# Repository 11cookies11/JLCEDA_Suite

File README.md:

# KiCad Agent Suite

Agent-assisted KiCad hardware development pipeline.

KiCad Agent Suite uses a structured source model to resolve parts, compile an
intermediate representation, validate it, and export KiCad projects.

## Software Architecture

The suite is organized as a layered toolchain. AI agents and humans edit a
structured circuit model, then the toolchain derives build artifacts, validation
reports, and KiCad output from that source.

```text
AI agent / human
  |
  v
CLI and agent entrypoints
  src/kicad_suite/cli.py
  src/kicad_suite/entrypoints/
  |
  v
Orchestration layer
  src/kicad_suite/orchestration/
  - workflow templates, task routing, pipeline coordination, post-processing
  |
  v
Application services
  src/kicad_suite/application_services/
  - project state, diagnostics, reports, part resolution, semantic gates
  |
  v
Domain core
  src/kicad_suite/domain/core/
  - circuit model IO, IR compiler, IR validator, netlist, simulation plan,
    pin management, KiCad execution plan
  |
  v
Adapters
  src/kicad_suite/adapters/
  - KiCad writers/runners, PCB generation, JLC/LCSC/EasyEDA, symbol and
    footprint resolution
  |
  v
Generated build/output artifacts
```

### Main Data Flow

```text
source/circuit-model.source.json
  -> resolve parts and project-local libraries
  -> build/circuit-model.resolved.json
  -> build/ir.v1.json
  -> build/ir-validation.json
  -> hardware semantic gate artifacts
     build/net-intents.v1.json
     build/pin-contracts.v1.json
     build/hardware-erc.v1.json
     build/export-gate.v1.json
  -> output/<topology>/*.kicad_*
  -> ERC classification and agent reports
  -> build/report.json and build/report.md
```

`source/circuit-model.source.json` is the only authoritative project model for
new projects. `build/` and `output/` are generated views of that source.

### Agent-Facing API

The stable agent entrypoint is:

```powershell
hwtool agent manifest
```

The `agent` command group exposes machine-readable lifecycle operations:

- `status`, `inspect`, `explain`, `diagnose`, `report`
- `build-ir`, `validate-ir`, `resolve-symbols`, `export-kicad`
- `run` and `patch` for controlled model edits through the Model API
- `workflow` for template-driven multi-step tasks
- `pins` for pin resource checks and assignments
- `jlc` for LCSC search, preview, and project-local downloads
- `semantic-gates` for listing, validating, proposing, and accepting semantic
  gate rules

Agents should prefer these commands over direct writes to generated artifacts.

### Validation and Gate Layers

The repository uses several validation layers with different responsibilities:

- IR validation checks structural correctness before KiCad export.
- Circuit sanity checks catch shorts, floating pins, and suspicious passives.
- Hardware semantic gates catch topology-level mistakes before export, such as
  missing USB-C CC pull-downs or unsafe power-path wiring.
- KiCad ERC runs on exported KiCad projects and is classified into agent-readable
  findings.
- Semantic gate proposals can be generated from hardware ERC findings and stored
  as reviewable project knowledge.

Semantic gate files live in:

```text
build/proposed-semantic-gates/*.gate.json   # generated review queue
source/semantic-gates/*.gate.json           # accepted project rules
resources/hardware-rules/builtin/           # reserved built-in rules
resources/hardware-rules/promoted/          # reserved promoted rules
```

### Source Tree Responsibilities

- `src/kicad_suite/cli.py`: command-line and agent command dispatch.
- `src/kicad_suite/domain/core/`: pure model compilation, validation, planning,
  and pin/resource logic.
- `src/kicad_suite/application_services/`: project-level services that combine
  domain logic with filesystem state, reports, diagnostics, and rule registries.
- `src/kicad_suite/orchestration/`: workflow templates, agent task generation,
  pipeline event logs, and build coordination.
- `src/kicad_suite/adapters/`: integrations with KiCad files/tools,
  EasyEDA/JLC/LCSC, symbol libraries, and PCB writers.
- `schemas/`: JSON schemas for source models, IR, API requests/results, reports,
  semantic gates, and generated sidecar artifacts.
- `scripts/`: standalone utility scripts, including the hardware semantic gate.
- `tests/`: regression tests for CLI commands, schemas, model APIs, semantic
  gates, KiCad generation, and fixture behavior.

## Project Layout

New projects use the split source/build layout:

```text
project/
  source/
    circuit-model.source.json
  build/
    circuit-model.resolved.json
    ir.v1.json
    ir-validation.json
    report.json
    report.md
  libraries/
    symbols/
    footprints/
    3dmodels/
  output/
    <topology>/
      <topology>.kicad_pro
      <topology>.kicad_sch
      <topology>.kicad_pcb
      <topology>.erc.json
      <topology>.erc.classification.json
      agent-report.json
```

Edit `source/circuit-model.source.json`. Treat `build/`, `output/`, logs, and
`project.state.json` as generated artifacts.

## Common Workflow

Run commands from a project directory:

```powershell
hwtool agent status --project .
hwtool agent inspect --project .
hwtool agent diagnose --project .
hwtool agent resolve-symbols --project . --timeout 120
hwtool agent build-ir --project .
hwtool agent validate-ir --project .
hwtool agent export-kicad --project .
hwtool agent report --project . --markdown
hwtool agent diagnose --project .
```

Do not export KiCad before IR validation passes.

## Examples

Editable example source models live under `examples/*/source/`.

- `examples/stm32f103-minimal-system/source/circuit-model.source.json`
- `examples/esp32c3-minimal-system/source/circuit-model.source.json`
- `examples/refactor-layout-demo/source/circuit-model.source.json`
- `examples/h618-agentboard-v1/source/circuit-model.source.json`

Generated example `build/`, `output/`, and downloaded project-local libraries are
not tracked in git. Regenerate them with the workflow above when needed.

## Development

Useful commands:

```powershell
python scripts/kas.py --help
python -m pytest
npm run jlc:search -- STM32F103C8T6
```

Repository-wide KiCad resource libraries live in `resources/kicad/`.

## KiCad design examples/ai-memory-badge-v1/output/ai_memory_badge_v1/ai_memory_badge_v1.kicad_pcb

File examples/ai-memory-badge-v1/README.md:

# AI Memory Badge V1

全天候随身 AI 记忆器原型项目。

本版本先定义产品需求和系统设计，不急于锁定完整原理图。目标是做一块可佩戴、可夹持、低功耗、以人声触发录音为核心的硬件原型板。

## Product Direction

- 形态：胸牌 / 夹子
- 录音策略：人声触发录音，支持手动标记重点片段
- 隐私策略：本地加密预留，录音状态可见，支持物理静音
- 同步方式：USB-C + Wi-Fi
- 设计优先级：续航优先，其次是可接受的人声清晰度
- 项目阶段：原型板，不追求第一版直接小型量产

## Documents

- `docs/00_requirements.md`：产品需求与约束
- `docs/01_system_architecture.md`：系统架构和模块划分
- `docs/02_design_decisions.md`：关键设计取舍
- `docs/03_hardware_design_plan.md`：硬件设计方案与验证计划
- `docs/04_component_selection.md`：Rev A 器件选型方向
- `docs/05_esp32s3_bare_chip_design.md`：ESP32-S3 裸芯片实现方案
- `docs/06_schematic_module_plan.md`：原理图模块拆分方案
- `docs/07_part_resolution_notes.md`：关键器件解析状态与候选料

## Next Step

确认需求后，下一步生成：

```text
source/circuit-model.source.json
```

并进入 KiCad Agent Suite 的标准流程：

```powershell
hwtool agent inspect --project .
hwtool agent resolve-symbols --project . --timeout 120
hwtool agent build-ir --project .
hwtool agent validate-ir --project .
hwtool agent export-kicad --project .
hwtool agent report --project . --markdown
```

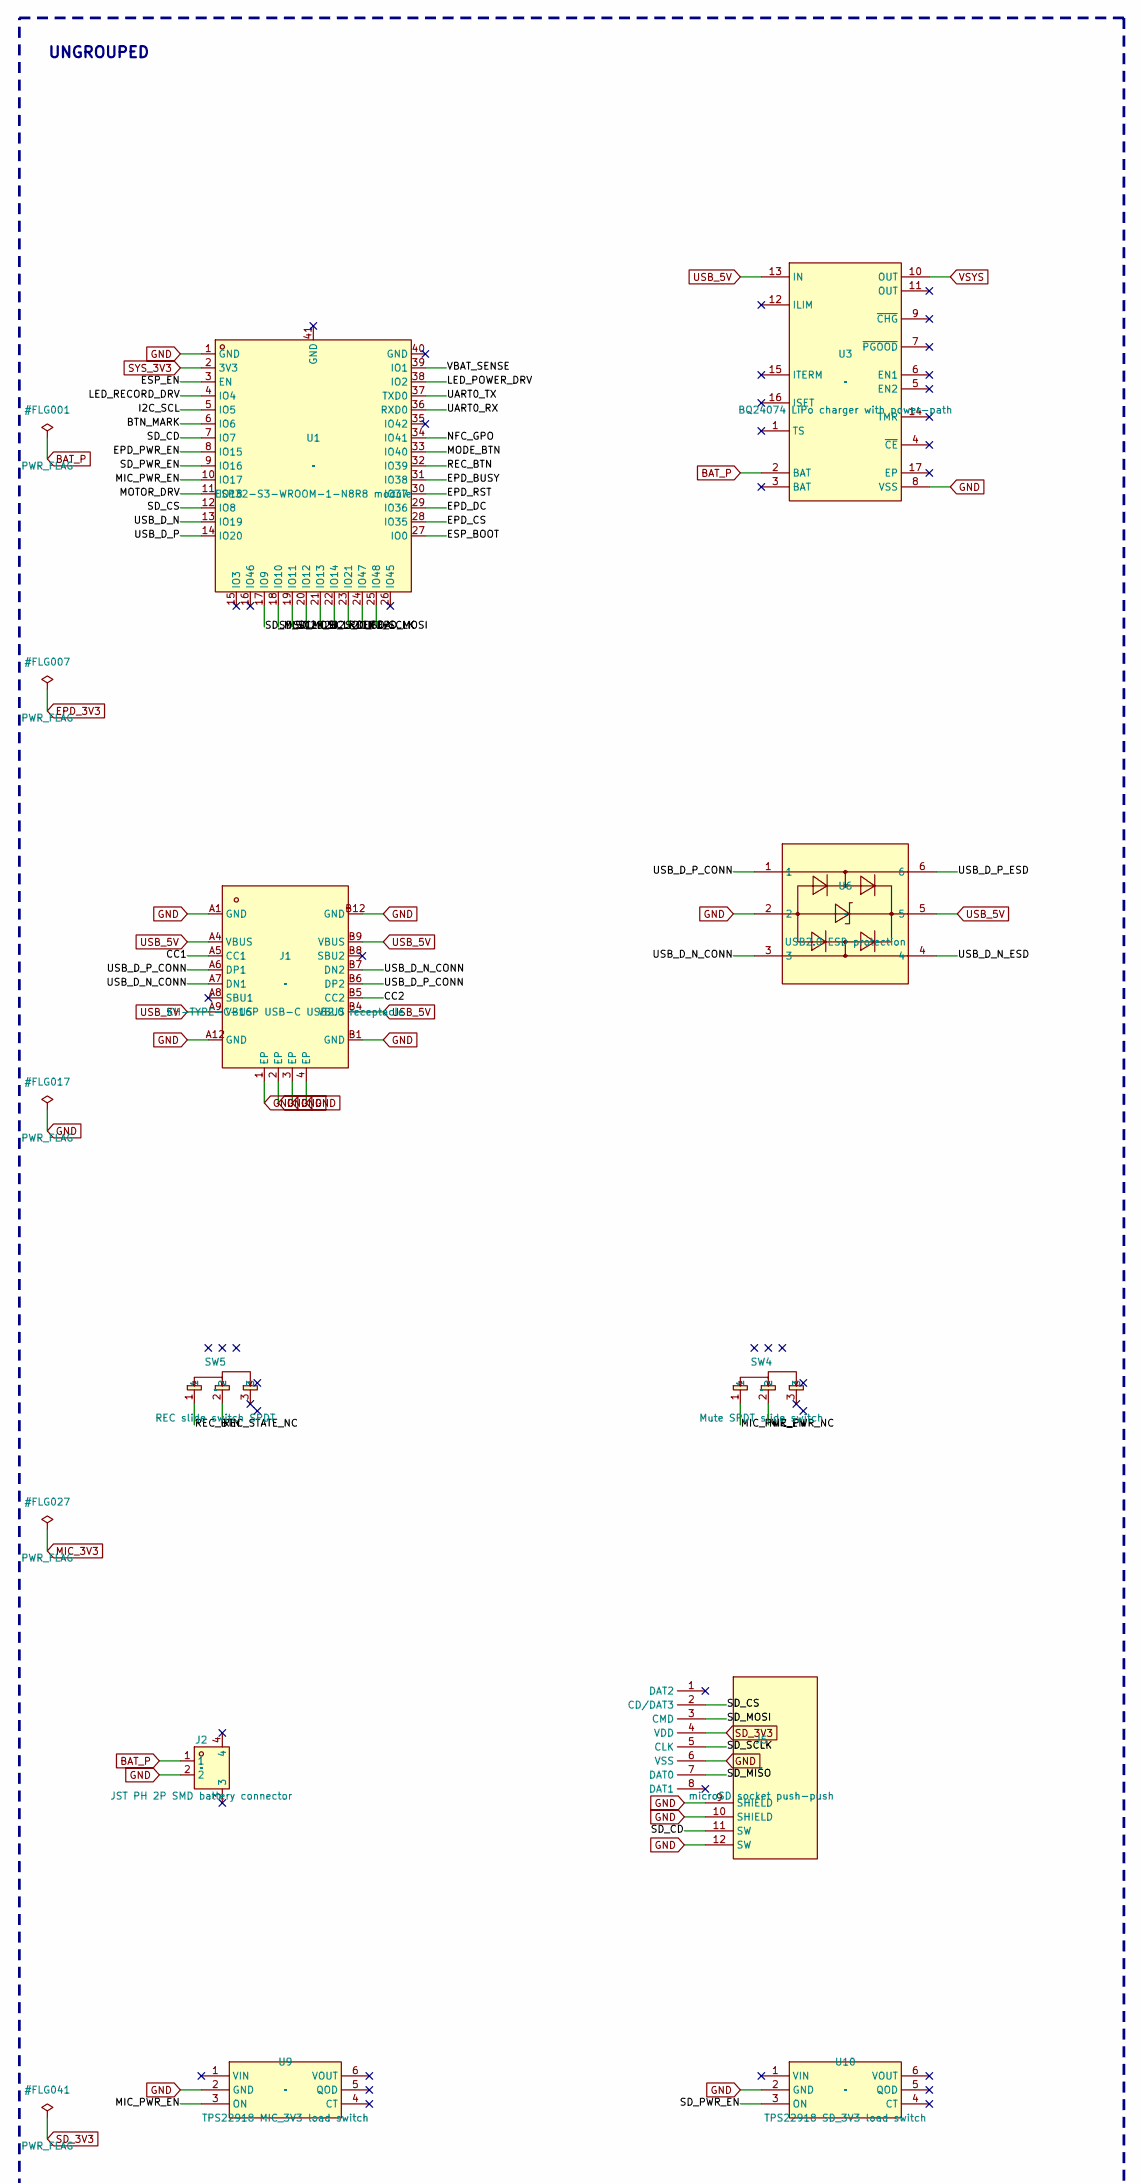
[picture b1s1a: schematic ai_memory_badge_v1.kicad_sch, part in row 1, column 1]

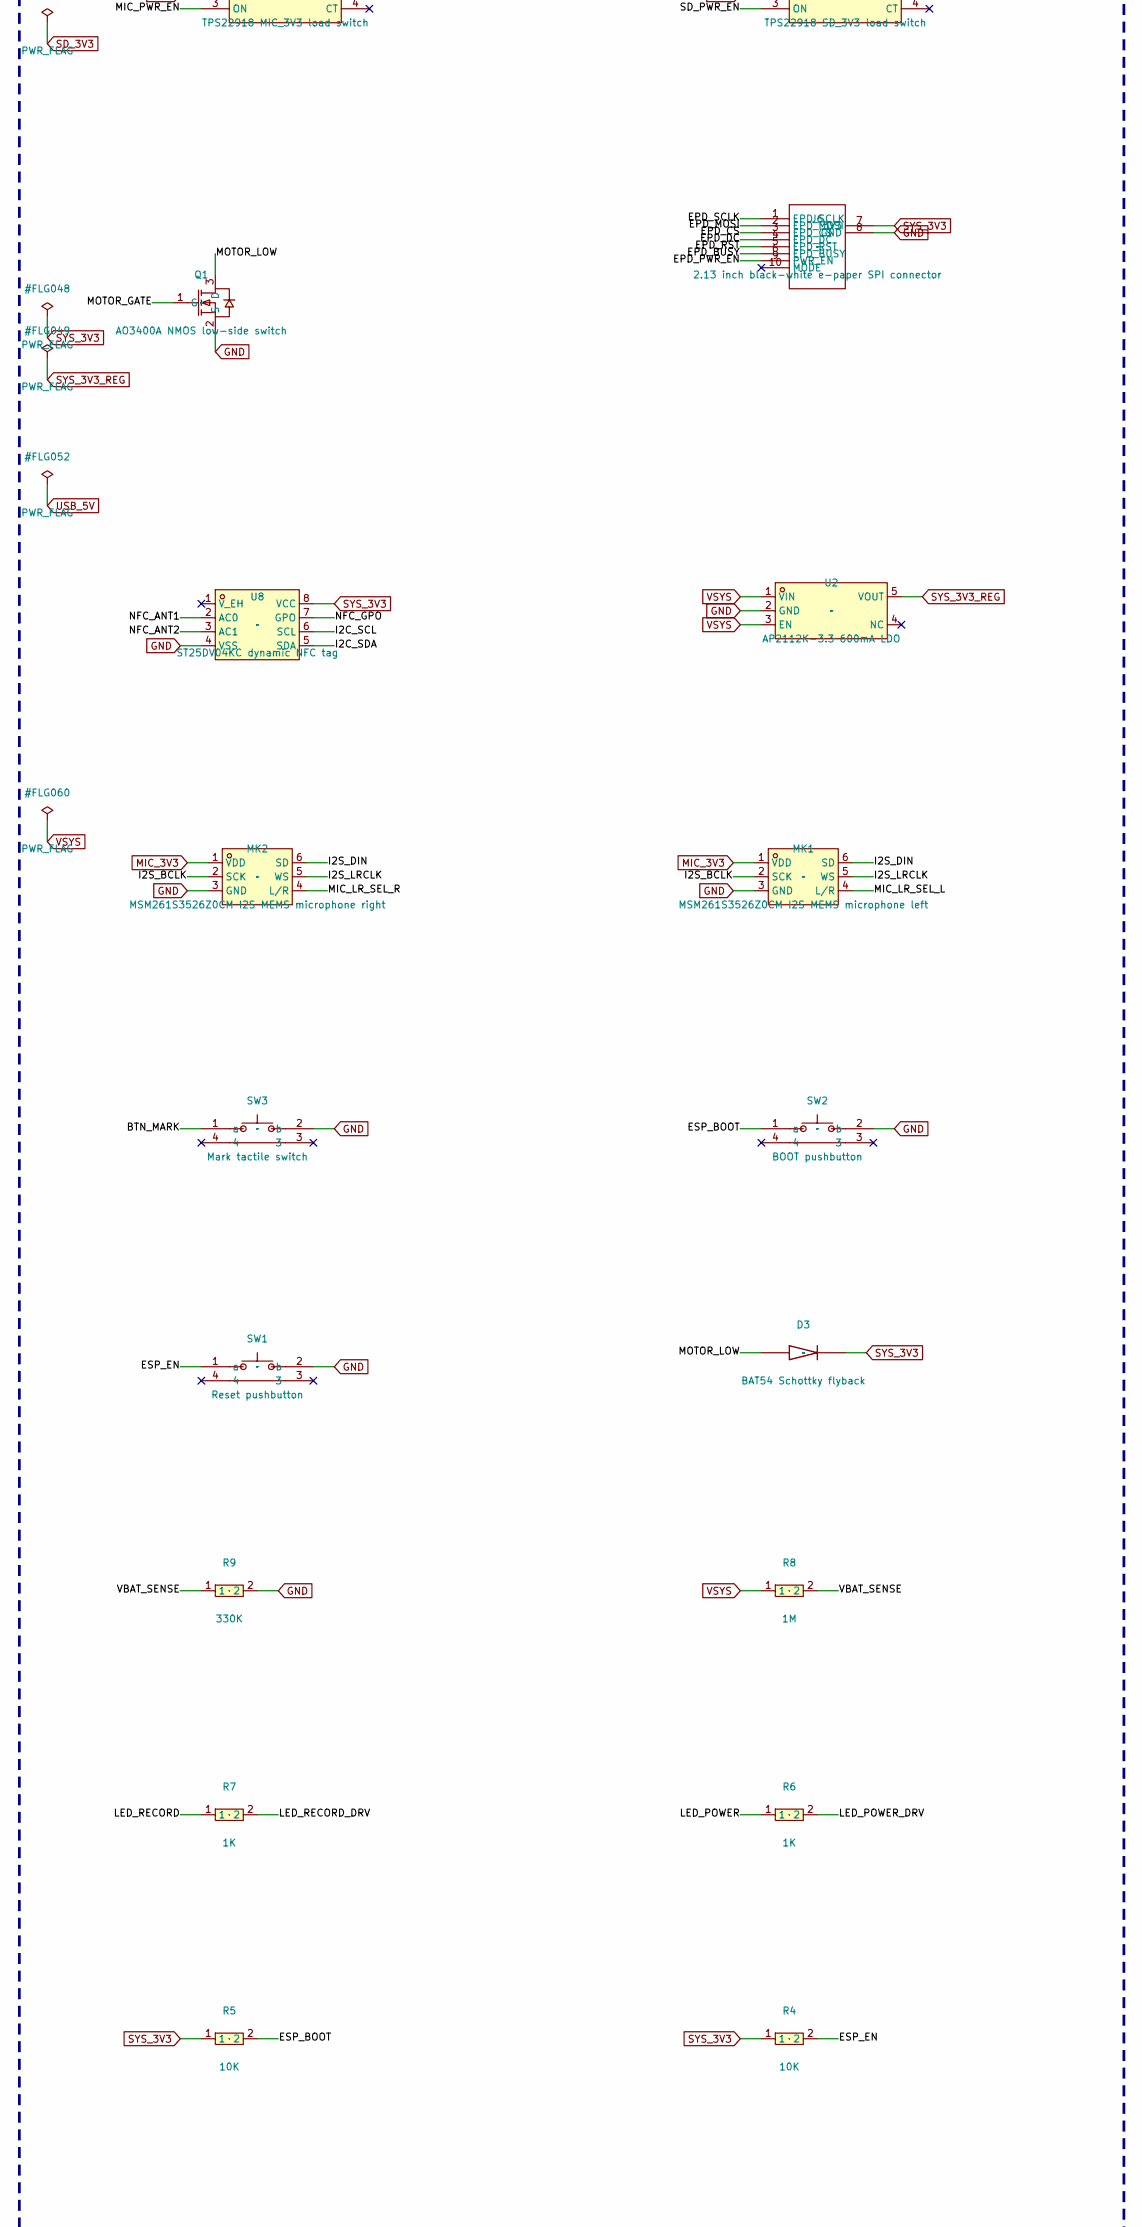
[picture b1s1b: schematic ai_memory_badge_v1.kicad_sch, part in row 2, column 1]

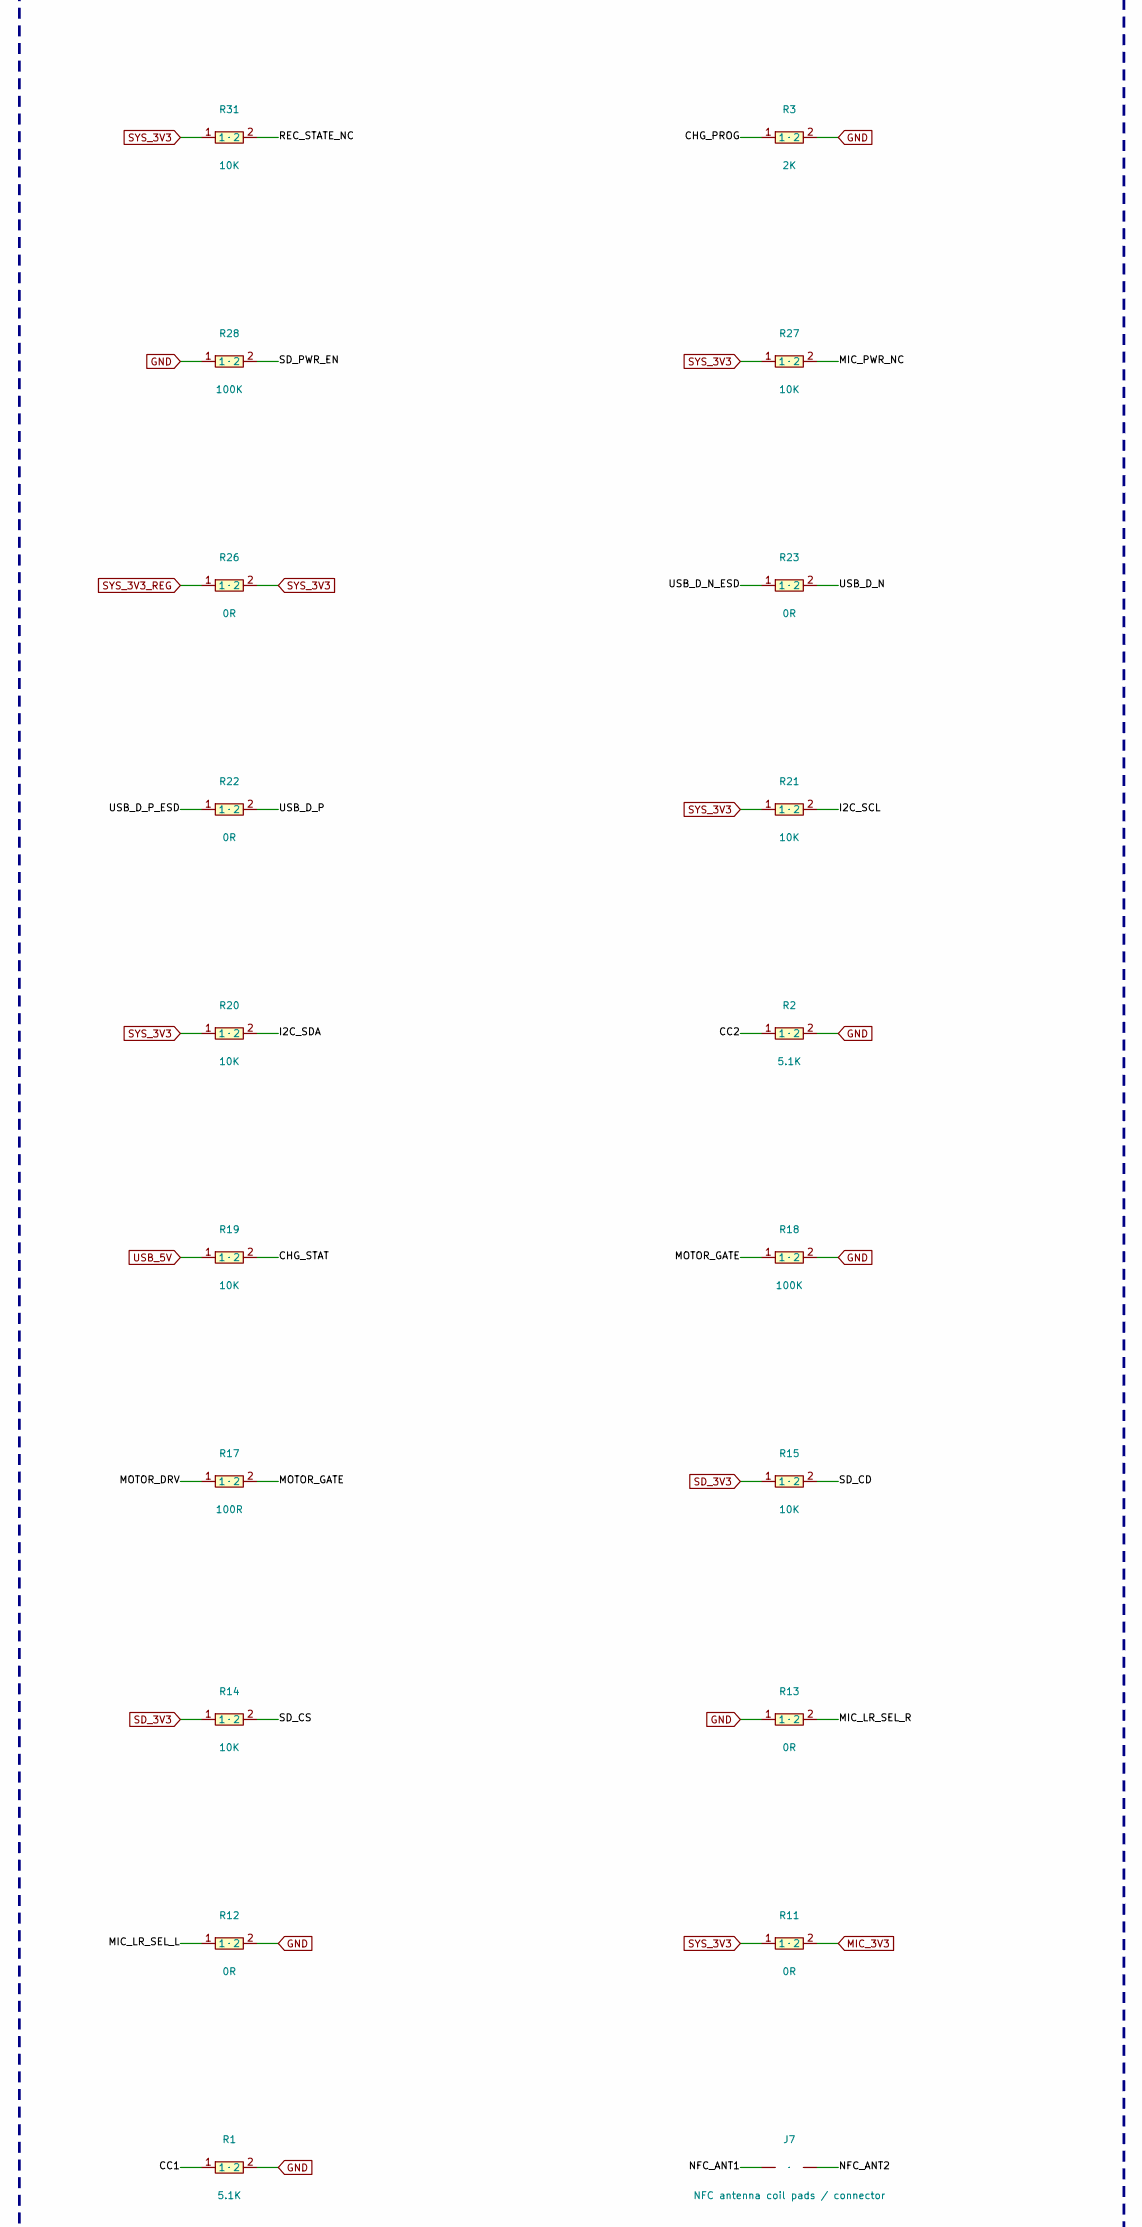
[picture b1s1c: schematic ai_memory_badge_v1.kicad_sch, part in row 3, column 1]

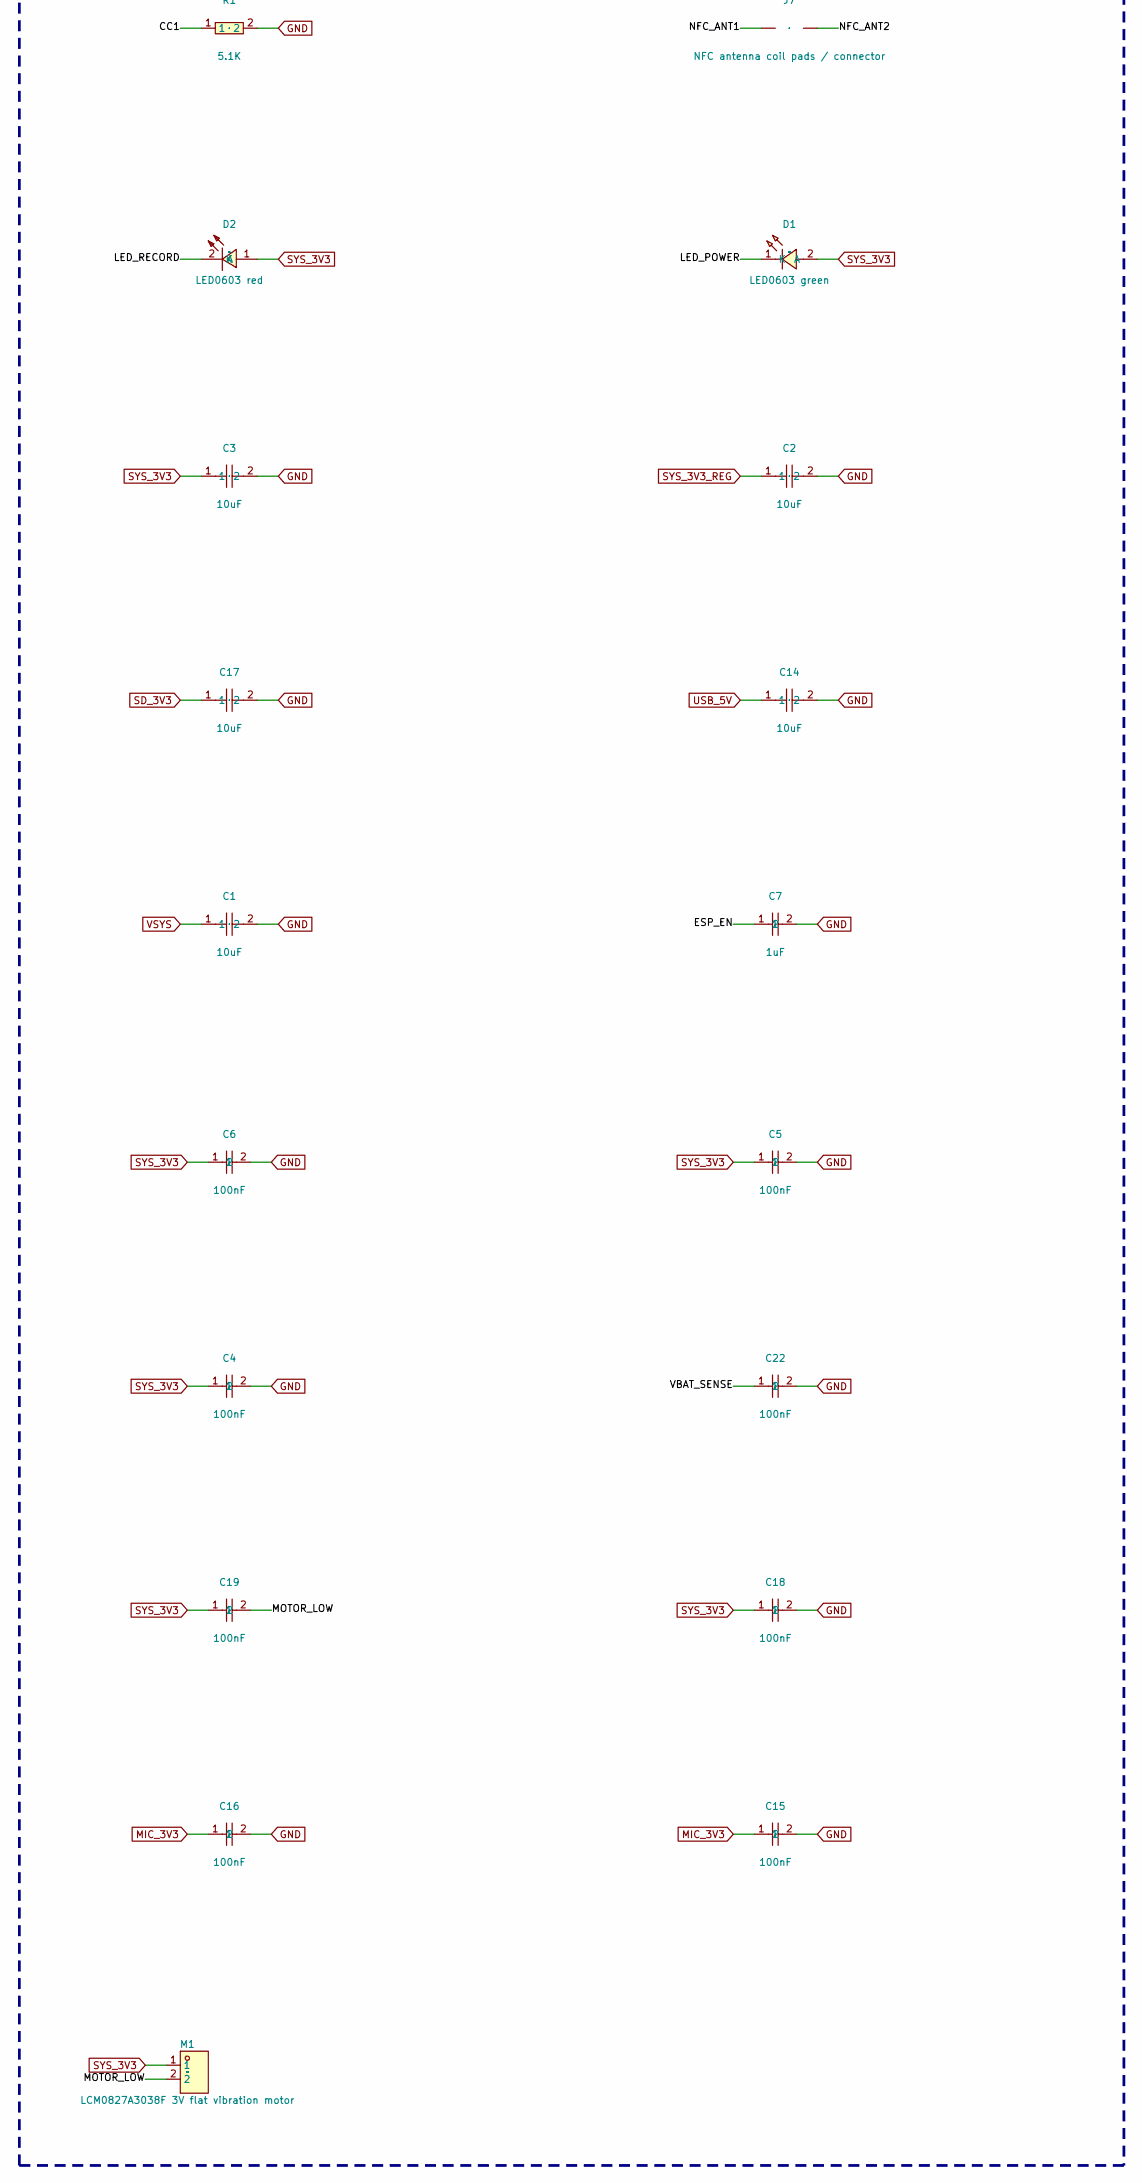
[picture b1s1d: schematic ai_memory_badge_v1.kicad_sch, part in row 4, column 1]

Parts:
C1, C2, C3, C14, C17: 10uF; C0603; LCSC C19702
C4, C5, C6, C15, C16, C18, C19, C22: 100nF; C0603; LCSC C1590
C7: 1uF; C0603; LCSC C1592
D1: LED0603 green; LED-SMD_L1.6-W0.8-RD_GREEN-1; LCSC C5139863
D2: LED0603 red; LED-SMD_L1.6-W0.8-R-RD; LCSC C2286
D3: BAT54 Schottky flyback; SOT-23-3_L2.9-W1.3-P1.90-LS2.4-BR; LCSC C131213
J1: KH-TYPE-C-16P USB-C USB2.0 receptacle; USB-C-SMD_KH-TYPE-C-16P; LCSC C709357
J2: JST PH 2P SMD battery connector; CONN-SMD_P2.00_S2B-PH-SM4-TB-LF-SN; LCSC C295747
J5: microSD socket push-push; TF-SMD_TF-001B; LCSC C125617
J6: 2.13 inch black-white e-paper SPI connector; FPC-SMD_24P-P0.50-L6.1-W16.4; LCSC C20688
J7: NFC antenna coil pads / connector; SMD-2P
M1: LCM0827A3038F 3V flat vibration motor; VIBRATIONMOTOR-TH_LCM0827A3038F; LCSC C2759981
MK1: MSM261S3526Z0CM I2S MEMS microphone left; MIC-SMD_6P-L3.5-W2.7-P0.90-TR; LCSC C966933
MK2: MSM261S3526Z0CM I2S MEMS microphone right; MIC-SMD_6P-L3.5-W2.7-P0.90-TR; LCSC C966933
Q1: AO3400A NMOS low-side switch; SOT-23-3_L2.9-W1.3-P1.90-LS2.4-BR; LCSC C20917
R1, R2: 5.1K; R0603; LCSC C23186
R3: 2K; R0603; LCSC C22975
R4, R5, R14, R15, R19, R20, R21, R27, R31: 10K; R0603; LCSC C15401
R6, R7: 1K; R0603; LCSC C14676
R8: 1M; R0603; LCSC C22935
R9: 330K; R0603; LCSC C23137
R11, R12, R13, R22, R23, R26: 0R; R0603; LCSC C21189
R17: 100R; R0603; LCSC C22775
R18, R28: 100K; R0603; LCSC C25803
SW1: Reset pushbutton; SW-SMD_K5-1617SA-02; LCSC C128964
SW2: BOOT pushbutton; SW-SMD_K5-1617SA-02; LCSC C128964
SW3: Mark tactile switch; SW-SMD_K5-1617SA-02; LCSC C128964
SW4: Mute SPDT slide switch; SW-SMD_MST-12D18G4-SPDT-SLIDE-SWITCH; LCSC C49023767
SW5: REC slide switch SPDT; SW-SMD_MST-12D18G4-SPDT-SLIDE-SWITCH; LCSC C49023767
U1: ESP32-S3-WROOM-1-N8R8 module; WIRELM-SMD_ESP32-S3-WROOM-1; LCSC C2913201
U2: AP2112K-3.3 600mA LDO; SOT-25-5_L2.9-W1.6-P0.95-LS2.8-BL; LCSC C51118
U3: BQ24074 LiPo charger with power-path; QFN-16_L3.0-W3.0-P0.50-TL-EP1.7; LCSC C54313
U6: USB2.0 ESD protection; SOT-23-6_L2.9-W1.6-P0.95-LS2.8-BL; LCSC C7519
U8: ST25DV04KC dynamic NFC tag; SO-8_L4.9-W3.9-P1.27-LS6.0-BL; LCSC C5221752
U9: TPS22918 MIC_3V3 load switch; SOT-23-6_L2.9-W1.6-P0.95-LS2.8-BL; LCSC C131941
U10: TPS22918 SD_3V3 load switch; SOT-23-6_L2.9-W1.6-P0.95-LS2.8-BL; LCSC C131941

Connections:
BAT_P: J2.1, U3.2 (BAT)
BTN_MARK: SW3.1 (a), U1.6 (IO6)
CC1: J1.A5 (CC1), R1.1
CC2: J1.B5 (CC2), R2.1
CHG_PROG: R3.1, U3.16 (ISET)
CHG_STAT: R19.2, U3.9 (~CHG)
EPD_BUSY: J6.6 (EPD_BUSY), U1.31 (IO38)
EPD_CS: J6.3 (EPD_CS), U1.28 (IO35)
EPD_DC: J6.4 (EPD_DC), U1.29 (IO36)
EPD_MOSI: J6.2 (EPD_MOSI), U1.25 (IO48)
EPD_PWR_EN: J6.9 (PWR_EN), U1.8 (IO15)
EPD_RST: J6.5 (EPD_RST), U1.30 (IO37)
EPD_SCLK: J6.1 (EPD_SCLK), U1.24 (IO47)
ESP_BOOT: R5.2, SW2.1 (a), U1.27 (IO0)
ESP_EN: C7.1, R4.2, SW1.1 (a), U1.3 (EN)
GND: C1.2, C2.2, C3.2, C4.2, C5.2, C6.2, C7.2, C14.2, C15.2, C16.2, C17.2, C18.2, C22.2, J1.1 (EP), J1.2 (EP), J1.3 (EP), J1.4 (EP), J1.A1 (GND), J1.A12 (GND), J1.B1 (GND), J1.B12 (GND), J2.2, J5.6 (VSS), J5.9 (SHIELD), J5.10 (SHIELD), J5.12 (SW), J6.8 (GND), MK1.3 (GND), MK2.3 (GND), Q1.2 (S), R1.2, R2.2, R3.2, R9.2, R12.2, R13.1, R18.2, R28.1, SW1.2 (b), SW2.2 (b), SW3.2 (b), U1.1 (GND), U2.2 (GND), U3.8 (VSS), U6.2, U8.4 (VSS), U9.2 (GND), U10.2 (GND)
I2C_SCL: R21.2, U1.5 (IO5), U8.6 (SCL)
I2C_SDA: R20.2, U1.23 (IO21), U8.5 (SDA)
I2S_BCLK: MK1.2 (SCK), MK2.2 (SCK), U1.20 (IO12)
I2S_DIN: MK1.6 (SD), MK2.6 (SD), U1.22 (IO14)
I2S_LRCLK: MK1.5 (WS), MK2.5 (WS), U1.21 (IO13)
LED_POWER: D1.1 (K), R6.1
LED_POWER_DRV: R6.2, U1.38 (IO2)
LED_RECORD: D2.2 (K), R7.1
LED_RECORD_DRV: R7.2, U1.4 (IO4)
MIC_3V3: C15.1, C16.1, MK1.1 (VDD), MK2.1 (VDD), R11.2, U9.6 (VOUT)
MIC_LR_SEL_L: MK1.4 (L/R), R12.1
MIC_LR_SEL_R: MK2.4 (L/R), R13.2
MIC_PWR_EN: SW4.1, U1.10 (IO17), U9.3 (ON)
MIC_PWR_NC: R27.2, SW4.2
MODE_BTN: U1.33 (IO40)
MOTOR_DRV: R17.1, U1.11 (IO18)
MOTOR_GATE: Q1.1 (G), R17.2, R18.1
MOTOR_LOW: C19.2, D3.1 (A), M1.2, Q1.3 (D)
NFC_ANT1: J7.1 (AC0), U8.2 (AC0)
NFC_ANT2: J7.2 (AC1), U8.3 (AC1)
NFC_GPO: U1.34 (IO41), U8.7 (GPO)
REC_BTN: SW5.1, U1.32 (IO39)
REC_STATE_NC: R31.2, SW5.2
SD_3V3: C17.1, J5.4 (VDD), R14.1, R15.1, U10.6 (VOUT)
SD_CD: J5.11 (SW), R15.2, U1.7 (IO7)
SD_CS: J5.2 (CD/DAT3), R14.2, U1.12 (IO8)
SD_MISO: J5.7 (DAT0), U1.17 (IO9)
SD_MOSI: J5.3 (CMD), U1.19 (IO11)
SD_PWR_EN: R28.2, U1.9 (IO16), U10.3 (ON)
SD_SCLK: J5.5 (CLK), U1.18 (IO10)
SYS_3V3: C3.1, C4.1, C5.1, C6.1, C18.1, C19.1, D1.2 (A), D2.1 (A), D3.2 (K), J6.7 (3V3), M1.1, R4.1, R5.1, R11.1, R20.1, R21.1, R26.2, R27.1, R31.1, U1.2 (3V3), U8.8 (VCC), U9.1 (VIN), U10.1 (VIN)
SYS_3V3_REG: C2.1, R26.1, U2.5 (VOUT)
UART0_RX: U1.36 (RXD0)
UART0_TX: U1.37 (TXD0)
USB_5V: C14.1, J1.A4 (VBUS), J1.A9 (VBUS), J1.B4 (VBUS), J1.B9 (VBUS), R19.1, U3.13 (IN), U6.5
USB_D_N: R23.2, U1.13 (IO19)
USB_D_N_CONN: J1.A7 (DN1), J1.B7 (DN2), U6.3
USB_D_N_ESD: R23.1, U6.4
USB_D_P: R22.2, U1.14 (IO20)
USB_D_P_CONN: J1.A6 (DP1), J1.B6 (DP2), U6.1
USB_D_P_ESD: R22.1, U6.6
VBAT_SENSE: C22.1, R8.2, R9.1, U1.39 (IO1)
VSYS: C1.1, R8.1, U2.1 (VIN), U2.3 (EN), U3.10 (OUT)

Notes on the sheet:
UNGROUPED

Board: 2 copper layers, 62 parts (0 on the bottom side), 54 nets, no tracks yet.

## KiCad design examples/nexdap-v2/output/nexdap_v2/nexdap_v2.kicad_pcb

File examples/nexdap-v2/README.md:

# nexdap-esp32c3-managed-rp2040-swd-coprocessor-v2

This example is a starter workspace for the nexdap-esp32c3-managed-rp2040-swd-coprocessor-v2 project.

Project intent:

- Start from a generic hardware project template
- Keep the workspace ready for schematic, PCB, release, and validation artifacts
- Let the hardware model define the actual target platform and BOM

Current status:

- Requirements captured in `docs/00_requirements.md`
- Architecture and bring-up documents are scaffolded
- Hardware workspaces are ready for detail work

Recommended next steps:

1. Freeze requirements in `docs/00_requirements.md`
2. Draft the system architecture in `docs/01_system_architecture.md`
3. Create `source/circuit-model.source.json` when the interface list is stable
4. Let the toolchain generate `build/circuit-model.resolved.json`

Generated project slug: `nexdap-v2`

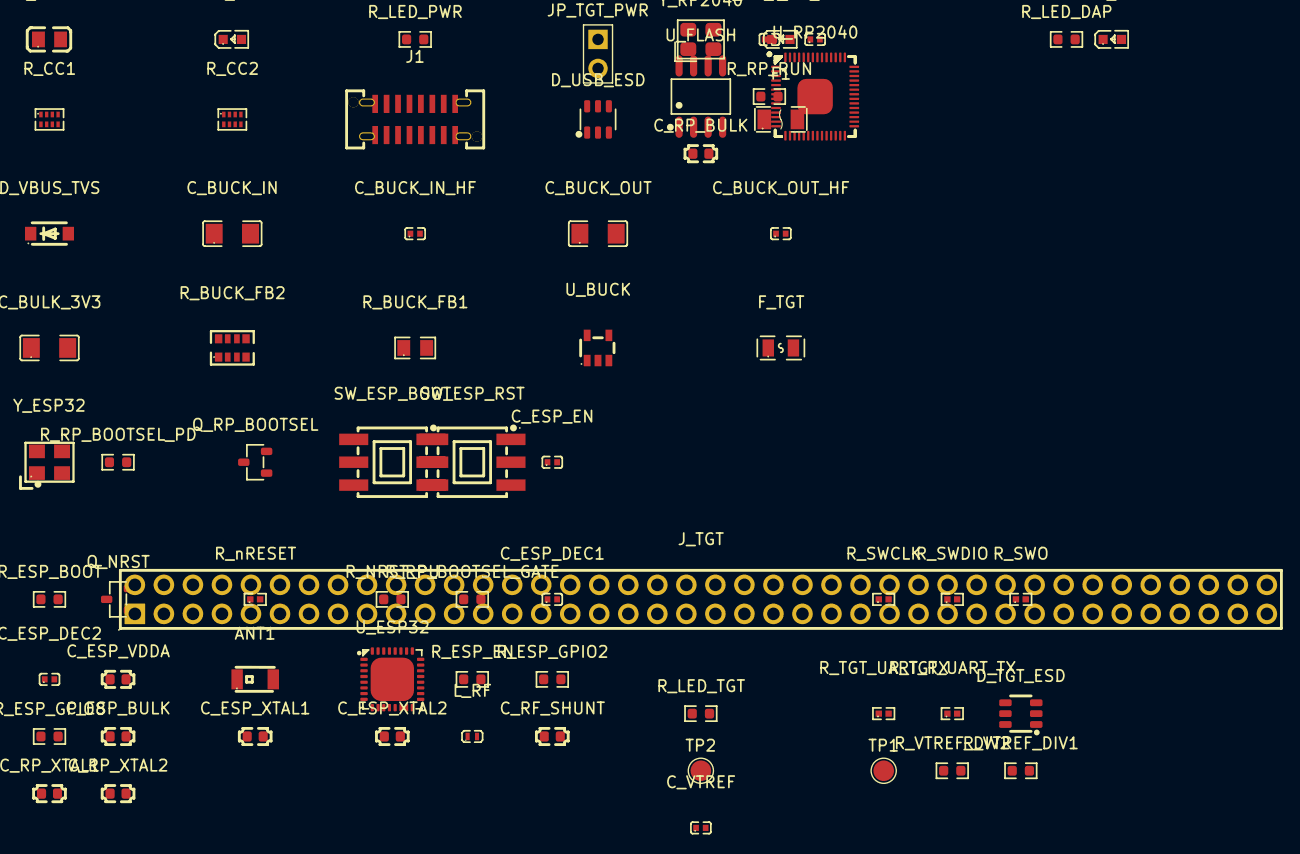
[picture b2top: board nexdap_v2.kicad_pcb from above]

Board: 2 copper layers, 68 parts (0 on the bottom side), 57 nets, no tracks yet.

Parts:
ANT1: 2450AT18A100E; ANT-SMD_L3.2-W1.6
C_BUCK_IN: 22uF; C1206
C_BUCK_IN_HF: 100nF; C0402
C_BUCK_OUT: 22uF; C1206
C_BUCK_OUT_HF: 100nF; C0402
C_BULK_3V3: 22uF; C1206
C_ESP_BULK: 4.7uF; C0603
C_ESP_DEC1, C_ESP_DEC2: 0.1uF; C0402
C_ESP_EN: 0.1uF; C0402
C_ESP_VDDA: 1uF; C0603
C_ESP_XTAL1, C_ESP_XTAL2: 22pF; C0603
C_RF_SHUNT: 1.2pF; C0603
C_RP_BULK: 4.7uF; C0603
C_RP_DEC1, C_RP_DEC2: 0.1uF; C0402
C_RP_XTAL1, C_RP_XTAL2: 22pF; C0603
C_VTREF: 0.1uF; C0402
D_TGT_ESD: SRV05-4; SOT-23-6_L2.9-W1.6-P0.95-LS2.8-BR
D_USB_ESD: USBLC6-2SC6; SOT-23-6_L2.9-W1.6-P0.95-LS2.8-BL
D_VBUS_TVS: SMF5.0A; SOD-123F_L2.8-W1.8-LS3.7-RD
F1: SMD1206-050-33; F1206
F_TGT: 200mA; F0805
J1: USB-C-16P; USB-C-SMD_HX-TYPE-C-16P-180-LT-H13.0
JP_TGT_PWR: 2P-Jumper; HDR-TH_2P-P2.54-V-M
J_TGT: Header-2.54-2x5P; HDR-TH_80P-P2.54-V-M-R2-C40-S2.54
LED_DAP: Blue; LED0603-RD-YELLOW
LED_PWR: Green; LED0603-RD-YELLOW
LED_TGT: Red; LED0603-RD-YELLOW
L_BUCK: 2.2uH; L0805
L_RF: 3.9nH; IND-SMD_L1.2-W0.7
Q_NRST: 2N7002; SOT-23-3_L2.9-W1.3-P1.90-LS2.4-BR
Q_RP_BOOTSEL: 2N7002; SOT-23-3_L2.9-W1.3-P1.90-LS2.4-BR
R_BUCK_FB1: 453k; R0805
R_BUCK_FB2: 100k; RES-ARRAY-SMD_0603-8P-L3.2-W1.6-BL
R_CC1, R_CC2: 5.1k; RES-ARRAY-SMD_0402-8P-L2.0-W1.0-BL
R_ESP_BOOT: 10k; R0603
R_ESP_EN: 10k; R0603
R_ESP_GPIO2, R_ESP_GPIO8: 10k; R0603
R_LED_DAP: 330R; R0603
R_LED_PWR: 330R; R0603
R_LED_TGT: 330R; R0603
R_NRST_PU: 10k; R0603
R_RP_BOOTSEL_GATE: 100R; R0603
R_RP_BOOTSEL_PD: 100k; R0603
R_RP_RUN: 10k; R0603
R_SWCLK: 22R; R0402
R_SWDIO: 22R; R0402
R_SWO: 22R; R0402
R_TGT_UART_RX: 22R; R0402
R_TGT_UART_TX: 22R; R0402
R_VTREF_DIV1, R_VTREF_DIV2: 10k; R0603
R_nRESET: 22R; R0402
SW_ESP_BOOT: TK-6580S-2; SW-SMD_TK-6580S-2
SW_ESP_RST: TK-6580S-2; SW-SMD_TK-6580S-2
TP1, TP2: TP; TP-SMD_1P
U_BUCK: SY8089A1AAC; SOT-23-5_L2.9-W1.6-P0.95-LS2.8-BL
U_ESP32: ESP32-C3FH4X; QFN-32_L5.0-W5.0-P0.50-TL-EP3.7
U_FLASH: GD25Q16ETIGR; SOP-8_L4.9-W3.9-P1.27-LS6.0-BL
U_RP2040: RP2040; LQFN-56_L7.0-W7.0-P0.4-EP
Y_ESP32: 40MHz; OSC-SMD_4P-L3.2-W2.5-BL_SIT8008BI
Y_RP2040: 12MHz; CRYSTAL-SMD_4P-L3.2-W2.5-BL

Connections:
+1V1: C_RP_DEC2.1, U_RP2040.23, U_RP2040.45, U_RP2040.50
+3V3_MAIN: C_BUCK_OUT.1, C_BUCK_OUT_HF.1, C_BULK_3V3.1, C_ESP_BULK.1, C_ESP_DEC1.1, C_ESP_DEC2.1, C_ESP_VDDA.1, C_RP_BULK.1, C_RP_DEC1.1, L_BUCK.2, R_BUCK_FB1.1, R_ESP_BOOT.1, R_ESP_EN.1, R_ESP_GPIO2.1, R_ESP_GPIO8.1, R_LED_DAP.1, R_LED_PWR.1, R_RP_RUN.1, U_ESP32.2, U_ESP32.3, U_ESP32.11, U_ESP32.17, U_ESP32.31, U_ESP32.32, U_FLASH.8, U_RP2040.1, U_RP2040.10, U_RP2040.22, U_RP2040.33, U_RP2040.42, U_RP2040.43, U_RP2040.44, U_RP2040.48, U_RP2040.49
+5V_SW_TGT: JP_TGT_PWR.2, J_TGT.9, R_LED_TGT.1
+5V_TGT_FUSED: F_TGT.2, JP_TGT_PWR.1
+5V_USB_PROTECTED: C_BUCK_IN.1, C_BUCK_IN_HF.1, D_USB_ESD.5, F1.2, F_TGT.1, U_BUCK.1, U_BUCK.4
BUCK_FB: R_BUCK_FB1.2, R_BUCK_FB2.1, U_BUCK.5
DAP_ACTIVITY: LED_DAP.1, U_RP2040.17
ESP_CHIP_EN: C_ESP_EN.1, R_ESP_EN.2, SW_ESP_RST.1, SW_ESP_RST.2, SW_ESP_RST.3, U_ESP32.7
ESP_GPIO8: R_ESP_GPIO8.2, U_ESP32.14
ESP_GPIO9_BOOT: R_ESP_BOOT.2, SW_ESP_BOOT.1, SW_ESP_BOOT.2, SW_ESP_BOOT.3, U_ESP32.15
ESP_RF_OUT: L_RF.1, U_ESP32.1
ESP_RP_BOOTSEL_CTRL: R_RP_BOOTSEL_GATE.1, U_ESP32.27
ESP_RP_RUN_CTRL: R_RP_RUN.2, U_ESP32.8, U_RP2040.26
ESP_RP_SWCLK: U_ESP32.9, U_RP2040.24
ESP_RP_SWDIO: R_ESP_GPIO2.2, U_ESP32.6, U_RP2040.25
ESP_SPI_CS: U_ESP32.12, U_RP2040.12
ESP_SPI_MISO: U_ESP32.13, U_RP2040.11
ESP_SPI_MOSI: U_ESP32.16, U_RP2040.5
ESP_SPI_SCLK: U_ESP32.10, U_RP2040.4
ESP_XTAL_N: C_ESP_XTAL2.1, U_ESP32.29, Y_ESP32.2
ESP_XTAL_P: C_ESP_XTAL1.1, U_ESP32.30, Y_ESP32.1
GND_HOST: ANT1.1, C_BUCK_IN.2, C_BUCK_IN_HF.2, C_BUCK_OUT.2, C_BUCK_OUT_HF.2, C_BULK_3V3.2, C_ESP_BULK.2, C_ESP_DEC1.2, C_ESP_DEC2.2, C_ESP_EN.2, C_ESP_VDDA.2, C_ESP_XTAL1.2, C_ESP_XTAL2.2, C_RF_SHUNT.2, C_RP_BULK.2, C_RP_DEC1.2, C_RP_DEC2.2, C_RP_XTAL1.2, C_RP_XTAL2.2, C_VTREF.2, D_TGT_ESD.2, D_USB_ESD.2, D_VBUS_TVS.2, J1.A1, J1.A12, J1.B1, J1.B12, J_TGT.6, J_TGT.10, LED_PWR.1, LED_TGT.1, Q_NRST.2, Q_RP_BOOTSEL.2, R_BUCK_FB2.2, R_CC1.2, R_CC2.2, R_RP_BOOTSEL_PD.2, R_VTREF_DIV2.2, SW_ESP_BOOT.4, SW_ESP_BOOT.5, SW_ESP_BOOT.6, SW_ESP_RST.4, SW_ESP_RST.5, SW_ESP_RST.6, U_BUCK.2, U_ESP32.33, U_FLASH.4, U_RP2040.19, U_RP2040.57
HOST_nRESET_CTRL: Q_NRST.1, U_RP2040.15
LED_DAP_A: LED_DAP.2, R_LED_DAP.2
LED_PWR_A: LED_PWR.2, R_LED_PWR.2
LED_TGT_K: LED_TGT.2, R_LED_TGT.2
L_BUCK_SW: L_BUCK.1, U_BUCK.3
QSPI_SCLK: U_FLASH.6, U_RP2040.52
QSPI_SD0: U_FLASH.5, U_RP2040.53
QSPI_SD1: U_FLASH.2, U_RP2040.55
QSPI_SD2: U_FLASH.3, U_RP2040.54
QSPI_SD3: U_FLASH.7, U_RP2040.51
RF_ANT: ANT1.2, C_RF_SHUNT.1, L_RF.2
RP_BOOTSEL_GATE: Q_RP_BOOTSEL.1, R_RP_BOOTSEL_GATE.2, R_RP_BOOTSEL_PD.1
RP_BOOTSEL_QSPI_SS: Q_RP_BOOTSEL.3, U_FLASH.1, U_RP2040.56
RP_TGT_SWCLK: R_SWCLK.1, U_RP2040.2
RP_TGT_SWDIO: R_SWDIO.1, U_RP2040.3
RP_TGT_UART_RX: R_TGT_UART_RX.2, U_RP2040.9
RP_TGT_UART_TX: R_TGT_UART_TX.1, U_RP2040.8
RP_TO_ESP_IRQ: U_ESP32.28, U_RP2040.14
RP_XIN: C_RP_XTAL1.1, U_RP2040.20, Y_RP2040.1
RP_XOUT: C_RP_XTAL2.1, U_RP2040.21, Y_RP2040.2
TGT_SWCLK: D_TGT_ESD.3, J_TGT.3, R_SWCLK.2, TP2.1
TGT_SWDIO: D_TGT_ESD.1, J_TGT.2, R_SWDIO.2, TP1.1
TGT_SWO_IN: R_SWO.1, U_RP2040.7
TGT_SWO_OUT: D_TGT_ESD.6, J_TGT.4, R_SWO.2
TGT_UART_RX: J_TGT.8, R_TGT_UART_RX.1
TGT_UART_TX: J_TGT.7, R_TGT_UART_TX.2
TGT_nRESET: D_TGT_ESD.4, J_TGT.5, R_nRESET.2
TGT_nRESET_DRV: Q_NRST.3, R_NRST_PU.2, R_nRESET.1
USB_CC1: J1.A5, R_CC1.1
USB_CC2: J1.B5, R_CC2.1
USB_DM: D_USB_ESD.3, J1.A7, J1.B7, U_ESP32.25
USB_DP: D_USB_ESD.1, J1.A6, J1.B6, U_ESP32.26
USB_VBUS: D_VBUS_TVS.1, F1.1, J1.A4, J1.A9, J1.B4, J1.B9
VTREF_ADC: C_VTREF.1, R_VTREF_DIV1.2, R_VTREF_DIV2.1, U_RP2040.38
VTREF_TARGET: D_TGT_ESD.5, J_TGT.1, R_NRST_PU.1, R_VTREF_DIV1.1

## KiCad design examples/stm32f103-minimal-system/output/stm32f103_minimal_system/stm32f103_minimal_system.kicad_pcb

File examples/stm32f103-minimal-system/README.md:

# STM32F103 Minimal System

Verified example for the current KiCad Agent Suite project protocol.

This project models a compact STM32F103C8T6 minimum system board with power input,
3.3 V regulation, reset and boot straps, SWD programming, USB, user LED, and board
edge expansion headers.

## Source Of Truth

Edit this file only:

```text
source/circuit-model.source.json
```

Generated files are kept for inspection and KiCad handoff:

```text
output/stm32f103_minimal_system/
```

Do not edit generated `build/`, `output/`, or `project.state.json` files manually.

## Rebuild

Run from this example directory:

```powershell
hwtool agent status --project .
hwtool agent inspect --project .
hwtool agent resolve-symbols --project . --timeout 120
hwtool agent build-ir --project .
hwtool agent validate-ir --project .
hwtool agent export-kicad --project .
hwtool agent report --project . --markdown
hwtool agent diagnose --project .
```

## Current Verification

- `build-ir`: 18 components, 10 nets
- `validate-ir`: ok, 0 errors, 0 warnings
- `export-kicad`: generated schematic, PCB, ERC, and report artifacts
- `diagnose`: no must-fix issues

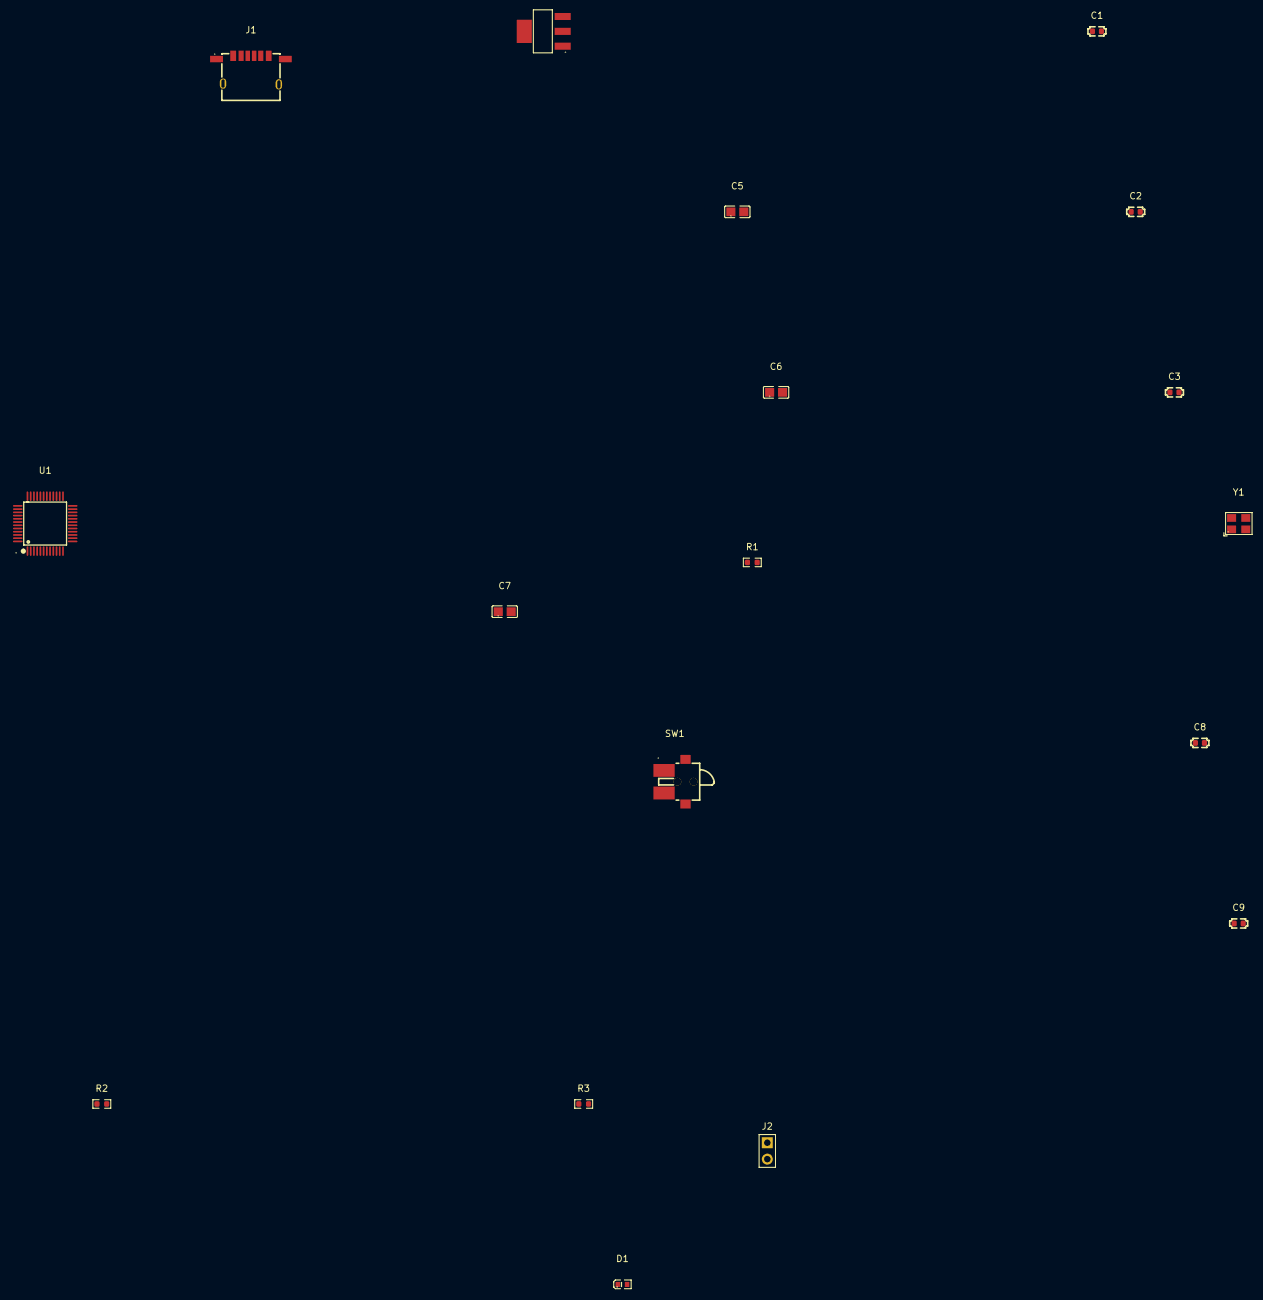
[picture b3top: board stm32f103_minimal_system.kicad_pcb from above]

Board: 2 copper layers, 18 parts (0 on the bottom side), 9 nets, no tracks yet.

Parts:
C1, C2, C3: 100nF; C0603
C5, C6, C7: 10uF; C0805
C8, C9: 22pF; C0603
D1: LED0603; LED-SMD_L1.6-W0.8-RD_GREEN-1
J1: USB-C16PIN; USB-C-SMD_USB-TYPE-C-006
J2: SWD-4P; HDR-TH_2P-P2.54-V-M
R1, R2: 10K; R0603
R3: 1K; R0603
SW1: SW-SMD_6x6; SW-SMD_K5-1617SA-02
U1: STM32F103C8T6; LQFP-48_L7.0-W7.0-P0.50-LS9.0-BL
U2: AMS1117-3.3; SOT-223-3_L6.5-W3.4-P2.30-LS7.0-BR
Y1: 8MHz; OSC-SMD_4P-L3.2-W2.5-BL

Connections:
+3V3: C1.1, C2.1, C3.1, C5.1, C7.1, D1.1, J2.1, R1.1, U1.1, U1.9, U1.24, U1.36, U1.48, U2.4
+5V: J1.1, U2.1
BOOT0: R2.1, U1.44
GND: C1.2, C2.2, C3.2, C5.2, C6.2, C7.2, C8.2, C9.2, D1.2, J1.2, R2.2, R3.2, SW1.2, U1.2, U1.8, U1.23, U1.35, U1.47, U2.2
HSE_IN: C8.1, U1.5, Y1.1
HSE_OUT: C9.1, U1.6, Y1.3
LED: R3.1, U1.13
NRST: R1.2, SW1.1, U1.7
SWDIO: J2.2, U1.34
